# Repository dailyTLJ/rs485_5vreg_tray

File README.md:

# rs485_5vreg_trayRS485 transceiver PCB with a 12V/5V voltage regulator, with footprints to plug in a TeensyLC and a BNO055 IMU (both Stemma and the old version, that's why there are two lines with reversed SDA/SCL pins).

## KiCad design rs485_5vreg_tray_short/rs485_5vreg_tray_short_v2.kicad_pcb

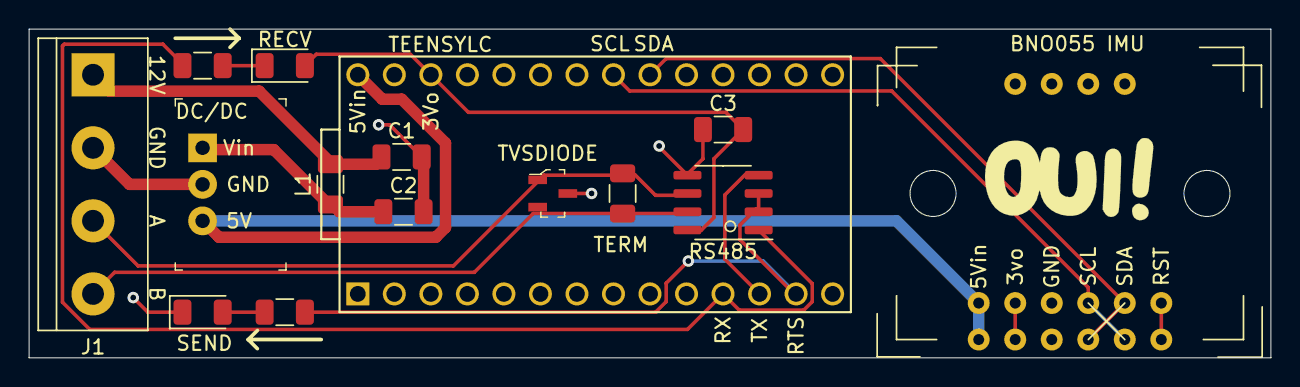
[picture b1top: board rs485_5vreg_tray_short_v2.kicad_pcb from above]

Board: 2 copper layers, 86.4 x 22.9 mm, 15 parts (0 on the bottom side), 14 nets.

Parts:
BNO055 IMU: BNO055_adafruit; BNO055_adafruit_bothversions
C1, C2: 10uF, 35V; C_1206_3216Metric
C3: 0.1uF; C_1206_3216Metric
DC/DC: TR05S05; 3-SIP_Module_V7805-500
J1: INPUT; TerminalBlock_bornier-4_P5.08mm
L1: 6.8uH; L_1206_3216Metric
R1, R2: R_US; R_1206_3216Metric
RECV: LED; LED_1206_3216Metric
RS485: MAX3072E; SOIC-8_3.9x4.9mm_P1.27mm
SEND: LED; LED_1206_3216Metric
TEENSYLC: Teensy-LC; Teensy_LC_sidesonly
TERM: 120; R_1206_3216Metric
TVSDIODE: TVSDIODE; SOT-23-3

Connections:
+3V3: C3.2, RECV.2, RS485.8, TEENSYLC.31
+5V: BNO055 IMU.1, DC/DC.3, TEENSYLC.33
/12V: C1.1, J1.1, L1.2
/A: J1.3, RS485.6, TERM.1, TVSDIODE.1
/B: J1.4, RS485.7, TERM.2, TVSDIODE.2
/RTS: R2.2, RS485.2, RS485.3, TEENSYLC.13
/RX: R1.2, RS485.1, TEENSYLC.11
/SCL0: BNO055 IMU.5, TEENSYLC.26
/SDA0: BNO055 IMU.4, TEENSYLC.25
/TX: RS485.4, TEENSYLC.12
GND: BNO055 IMU.3, C1.2, C2.2, C3.1, DC/DC.2, J1.2, RS485.5, SEND.1, TEENSYLC.1, TVSDIODE.3
unnamed: C2.1, DC/DC.1, L1.1
unnamed: R1.1, RECV.1
unnamed: R2.1, SEND.2

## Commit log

2022-04-26 imgs
2022-04-26 notes

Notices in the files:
rs485_5vreg_tray_short/rs485_5vreg_tray_short_v2.kicad_pcb:
DAiLY (c) 2022
